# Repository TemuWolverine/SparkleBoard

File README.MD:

# SparkleBoard 5v (WIP)
SparkleBoard is a USB-PD power board that provides two power rails - one is user selectable from 12v, 15v, 18v or 20v (if the USB-PD power brick supports it) by using jumpers. The other power rail is 5v for microcontrollers.

Amperage defaults to 2a, can be set to 3.25a by cutting JP1

## 5v  -> 3.3v
5v rail is provided via a buck converter - [AP63205](https://www.diodes.com/part/view/AP63205), an inexpensive fixed voltage buck converter from Diodes.

If you wanted 3.3v, this could be achieved by swapping out the chip for the AP63203, and changing the inductor to 3.9uH (from 4.7uH). The rest of the circuit design remains the same according to the manufacturer.

> Note: the AP63200/AP63201 are not fixed voltage output IC's and require additional circuitry with different values and are **NOT** drop in replacements.

## Datasheets
* [AP63205](https://www.diodes.com/datasheet/download/AP63200-AP63201-AP63203-AP63205.pdf)
* [HUSB238](https://www.hynetek.com/uploadfiles/site/219/news/aabbbbdb-48c9-4a44-a6dc-2c15f53282e6.pdf)

## References
* [Sparkfun Babybuck](https://github.com/sparkfun/Buck_Regulator_AP63203/tree/main) (AP6320***3***)
* [Adafruit HUSB238 breakout board](https://github.com/adafruit/Adafruit-USB-Type-C-Power-Delivery-Dummy-Breakout-PCB/tree/main)

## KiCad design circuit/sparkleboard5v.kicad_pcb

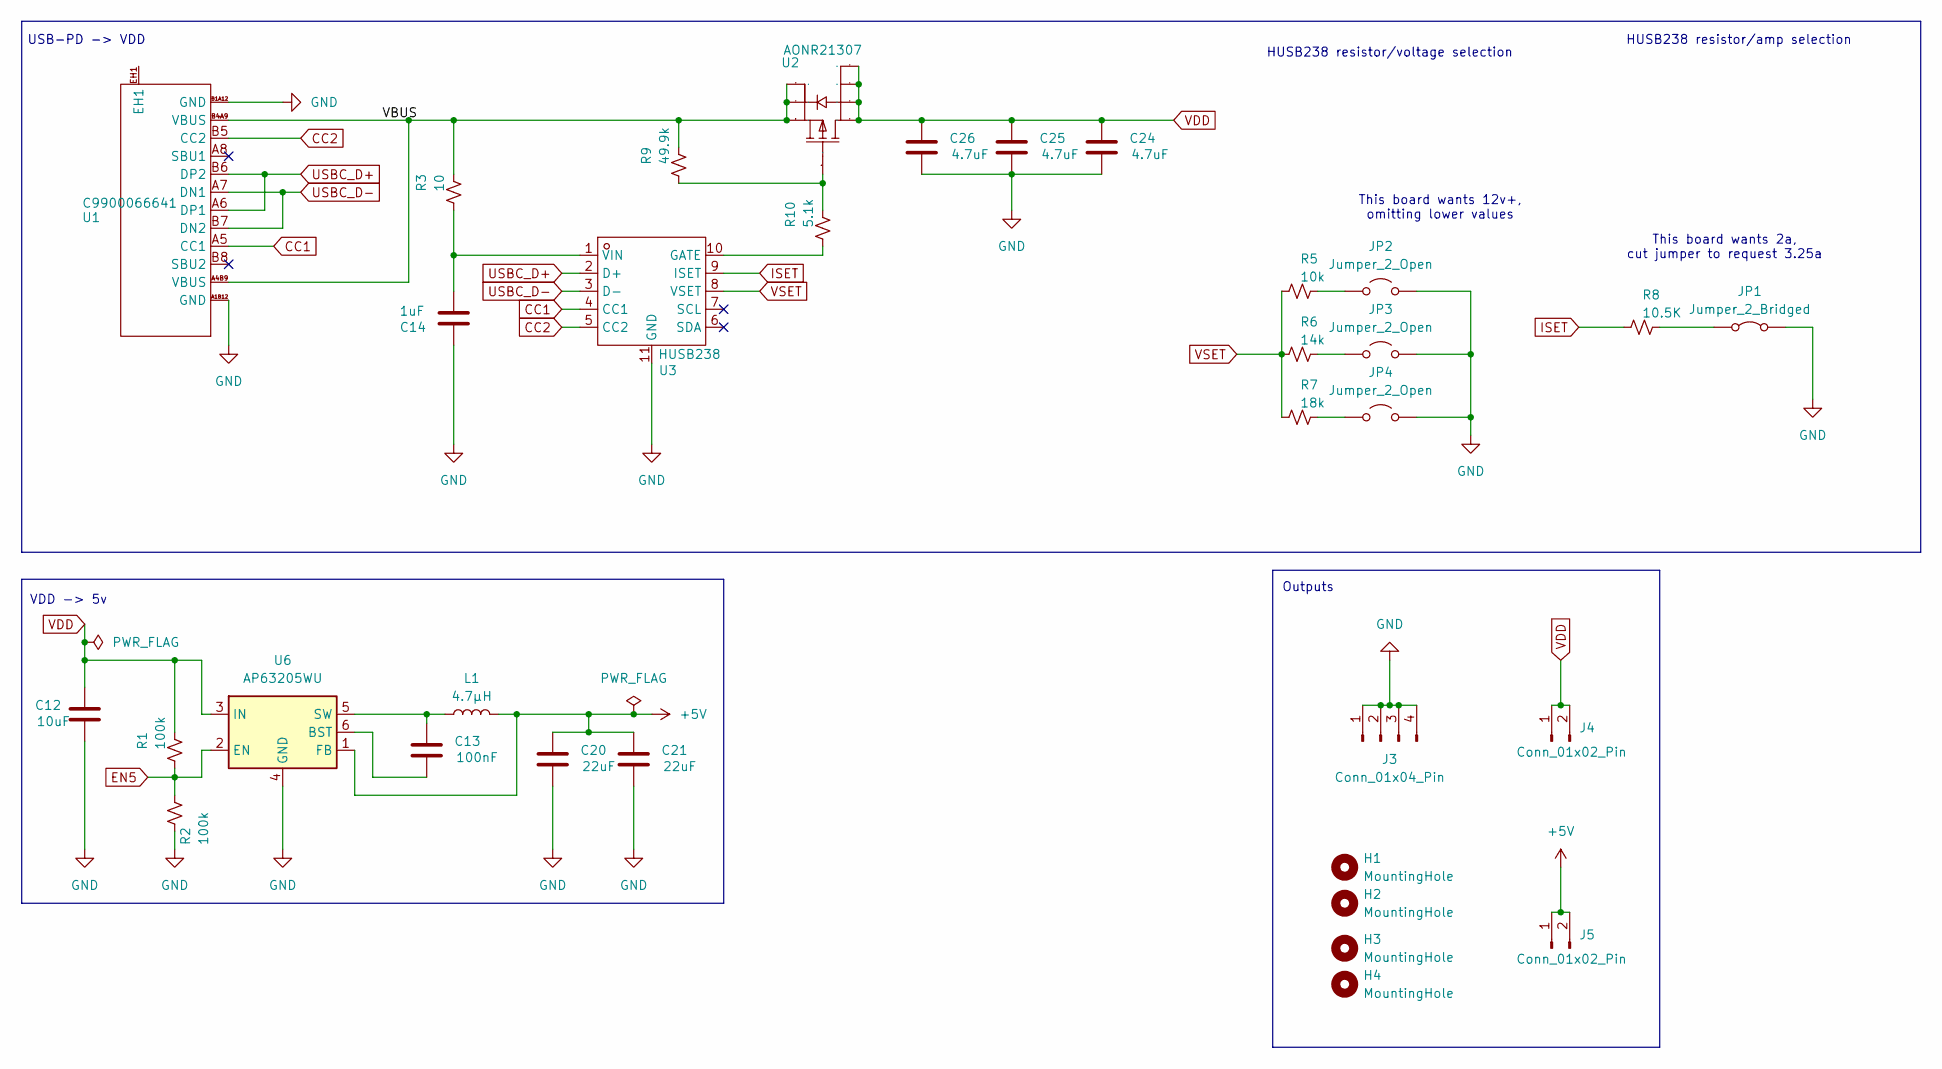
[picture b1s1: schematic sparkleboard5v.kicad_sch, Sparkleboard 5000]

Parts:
C12: 10uF; C_1210_3225Metric
C13: 100nF; C_0805_2012Metric
C14: 1uF; C_0805_2012Metric
C20, C21: 22uF; C_0805_2012Metric
C24, C25, C26: 4.7uF; C_0805_2012Metric
H1, H2, H3, H4: MountingHole; MountingHole_2.7mm_M2.5_DIN965_Pad
J3: Conn_01x04_Pin; PinHeader_1x04_P2.54mm_Vertical
J4, J5: Conn_01x02_Pin; PinHeader_1x02_P2.54mm_Vertical
JP1: Jumper_2_Bridged; SolderJumper-2_P1.3mm_Bridged_Pad1.0x1.5mm
JP2, JP3, JP4: Jumper_2_Open; SolderJumper-2_P1.3mm_Open_TrianglePad1.0x1.5mm
L1: 4.7μH; L_2010_5025Metric
R1, R2: 100k; R_0805_2012Metric
R3: 10; R_0603_1608Metric
R5: 10k; R_0603_1608Metric
R6: 14k; R_0603_1608Metric
R7: 18k; R_0603_1608Metric
R8: 10.5K; R_0805_2012Metric
R9: 49.9k; R_0603_1608Metric
R10: 5.1k; R_0603_1608Metric
U1: C9900066641; TYPE-C-SMD_UC.01.51-11-0017; Manufacturer Part UC.01.51-11-0017,typec; LCSC Part Name UC.01.51-11-0017,typec
U2: AONR21307; PRPAK-8_L3.0-W3.0-P0.65-BL-EP; Manufacturer Part AONR21307; LCSC Part Name 1个P沟道 耐压:30V 电流:24A
U3: HUSB238; TDFN-10_L3.0-W3.0-P0.50-TL-EP; Manufacturer Part HUSB238; LCSC Part Name HUSB238
U6: AP63205WU; TSOT-23-6

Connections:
+5V: C20.1, C21.1, J5.1, J5.2, L1.2, U6.1 (FB)
/VBUS: R3.2, R9.2, U1.A4B9 (VBUS), U1.B4A9 (VBUS), U2.1 (S), U2.2 (S), U2.3 (S)
CC1: U1.A5 (CC1), U3.4 (CC1)
CC2: U1.B5 (CC2), U3.5 (CC2)
EN5: R1.1, R2.2, U6.2 (EN)
GND: C12.2, C14.1, C20.2, C21.2, C24.2, C25.2, C26.2, J3.1, J3.2, J3.3, J3.4, JP1.2 (B), JP2.2 (B), JP3.2 (B), JP4.2 (B), R2.1, U1.A1B12 (GND), U1.B1A12 (GND), U3.11 (GND), U6.4 (GND); also elsewhere on the board
ISET: R8.1, U3.9 (ISET)
unnamed: JP2.1 (A), R5.2
unnamed: JP3.1 (A), R6.2
unnamed: JP4.1 (A), R7.2
unnamed 10: JP1.1 (A), R8.2; also elsewhere on the board
unnamed: R9.1, R10.2, U2.4 (G)
unnamed: R10.1, U3.10 (GATE)
unnamed: C14.2, R3.1, U3.1 (VIN)
unnamed: C13.2, U6.6 (BST)
unnamed: C13.1, L1.1, U6.5 (SW)
USBC_D+: U1.A6 (DP1), U1.B6 (DP2), U3.2 (D+)
USBC_D-: U1.A7 (DN1), U1.B7 (DN2), U3.3 (D-)
VDD: C12.1, C24.1, C25.1, C26.1, J4.1, J4.2, R1.2, U2.5 (D), U2.6 (D), U2.7 (D), U2.8 (D), U6.3 (IN)
VSET: R5.1, R6.1, R7.1, U3.8 (VSET)

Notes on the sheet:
HUSB238 resistor/amp selection
Outputs
USB-PD -> VDD
This board wants 2a, cut jumper to request 3.25a
This board wants 12v+, omitting lower values
VDD -> 5v
HUSB238 resistor/voltage selection

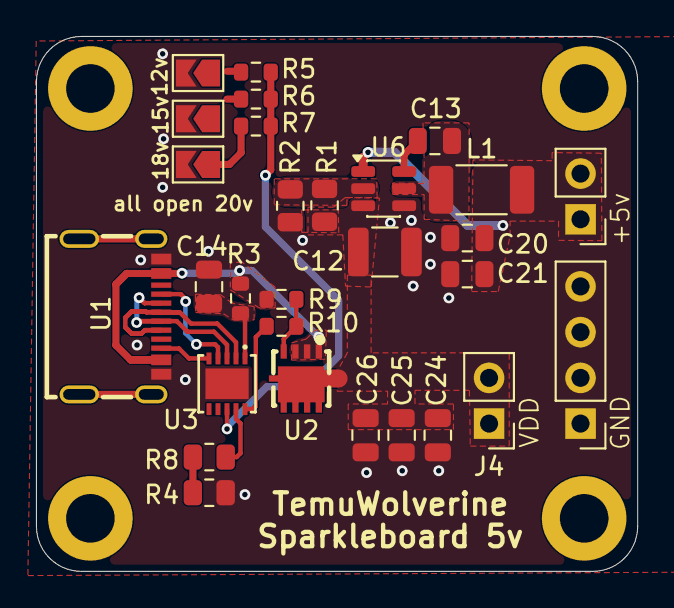
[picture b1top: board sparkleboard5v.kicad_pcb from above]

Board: 2 copper layers, 33.4 x 29.7 mm, 33 parts (0 on the bottom side), 20 nets.

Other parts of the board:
R4: 0; R_0805_2012Metric

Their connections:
GND: R4.1; also elsewhere on the board
unnamed 10: R4.2; also elsewhere on the board

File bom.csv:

Designator,Footprint,Quantity,Value,LCSC Part #
C12,1210,1,10uF,
C13,0805,1,100nF,
C14,0805,1,1uF,
"C20, C21",0805,2,22uF,
"C24, C25, C26",0805,3,4.7uF,
J3,PinHeader_1x04_P2.54mm_Vertical,1,Conn_01x04_Pin,
"J4, J5",PinHeader_1x02_P2.54mm_Vertical,2,Conn_01x02_Pin,
"JP2, JP3, JP4",SolderJumper-2_P1.3mm_Open_TrianglePad1.0x1.5mm,3,Jumper_2_Open,
L1,2010,1,4.7μH,
"R1, R2",0805,2,100k,
R10,0603,1,5.1k,
R3,0603,1,10,
R4,0805,1,0,
R5,0603,1,10k,
R6,0603,1,14k,
R7,0603,1,18k,
R8,0805,1,10.5K,
R9,0603,1,49.9k,
U1,TYPE-C-SMD_UC.01.51-11-0017,1,C9900066641,
U2,PRPAK-8_L3.0-W3.0-P0.65-BL-EP,1,AONR21307,
U3,TDFN-10_L3.0-W3.0-P0.50-TL-EP,1,HUSB238,
U6,TSOT-23-6,1,AP63205WU,

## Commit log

2026-06-10 happy with "v1"
2026-06-10 added basic readme
2026-06-12 tweaked spacing, updated readme
2026-06-26 Updated board, added more plots for reddit review
2026-06-26 updated gitignore to add bom
